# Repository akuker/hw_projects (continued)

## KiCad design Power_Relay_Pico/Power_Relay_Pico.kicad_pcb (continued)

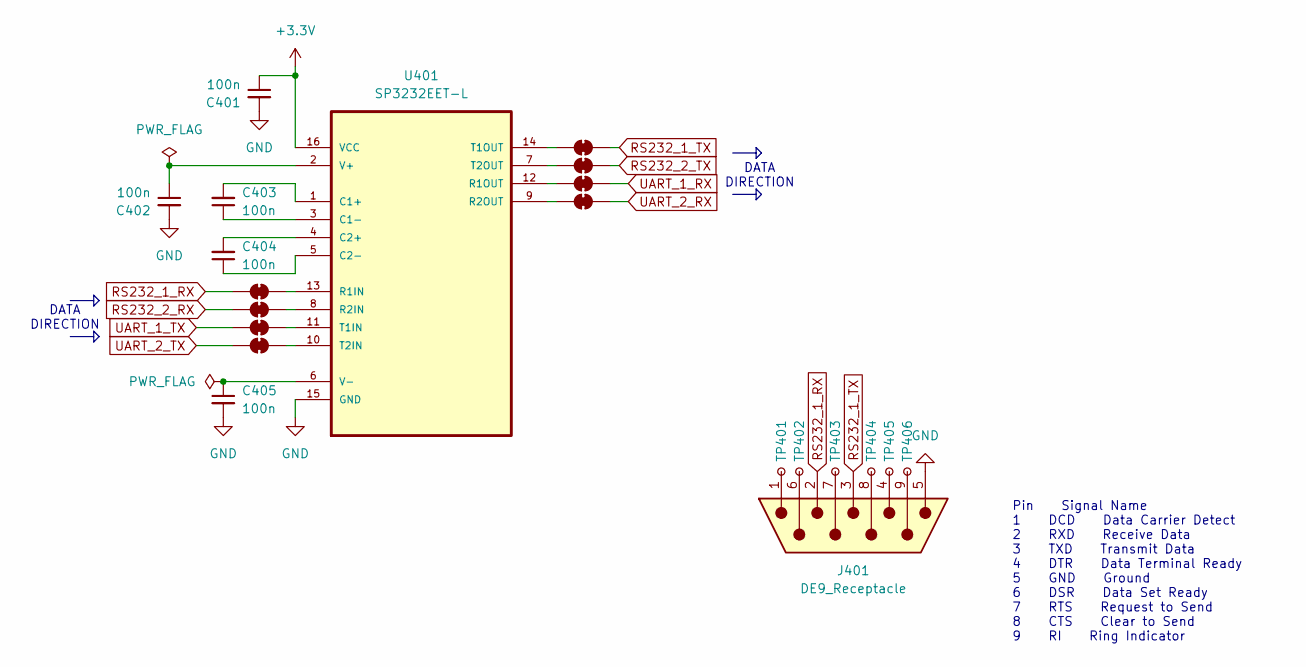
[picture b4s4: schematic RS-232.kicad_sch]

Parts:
C401, C402, C403, C404, C405: 100n; C_0603_1608Metric; LCSC C14663
J401: DE9_Receptacle; DSUB-9_Male_EdgeMount_P2.77mm; LCSC --
JP401, JP402, JP403, JP404, JP405, JP406, JP407, JP408: SolderJumper_2_Bridged; SolderJumper-2_P1.3mm_Bridged_RoundedPad1.0x1.5mm; LCSC --
TP401, TP402, TP403, TP404, TP405, TP406: TestPoint_Small; TestPoint_Pad_D1.0mm
U401: SP3232EET-L; TSSOP-16_4.4x5mm_P0.65mm; MPN SP3232EET-L; LCSC C13482

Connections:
+3.3V: C401.1, U401.16 (VCC); also elsewhere on the board
GND: C401.2, C402.2, C405.2, J401.5, U401.15 (GND); also elsewhere on the board
unnamed: J401.1, TP401.1
unnamed: J401.4, TP405.1
unnamed: J401.6, TP402.1
unnamed: J401.7, TP403.1
unnamed: J401.8, TP404.1
unnamed: J401.9, TP406.1
unnamed: JP401.1 (A), U401.14 (T1OUT)
unnamed: JP402.1 (A), U401.7 (T2OUT)
unnamed: JP403.1 (A), U401.12 (R1OUT)
unnamed: JP404.1 (A), U401.9 (R2OUT)
unnamed: JP405.2 (B), U401.13 (R1IN)
unnamed: JP406.2 (B), U401.8 (R2IN)
unnamed: JP407.2 (B), U401.11 (T1IN)
unnamed: JP408.2 (B), U401.10 (T2IN)
unnamed: C403.2, U401.1 (C1+)
unnamed: C403.1, U401.3 (C1-)
unnamed: C404.2, U401.4 (C2+)
unnamed: C404.1, U401.5 (C2-)
unnamed: C402.1, U401.2 (V+)
unnamed: C405.1, U401.6 (V-)
RS232_1_RX: J401.2, JP405.1 (A); also elsewhere on the board
RS232_1_TX: J401.3, JP401.2 (B); also elsewhere on the board
RS232_2_RX: JP406.1 (A); also elsewhere on the board
RS232_2_TX: JP402.2 (B); also elsewhere on the board
UART_1_RX: JP403.2 (B); also elsewhere on the board
UART_1_TX: JP407.1 (A); also elsewhere on the board
UART_2_RX: JP404.2 (B); also elsewhere on the board
UART_2_TX: JP408.1 (A); also elsewhere on the board

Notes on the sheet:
DATA DIRECTION
Pin Signal Name 1 DCD Data Carrier Detect 2 RXD Receive Data 3 TXD Transmit Data 4 DTR Data Terminal Ready 5 GND Ground 6 DSR Data Set Ready 7 RTS Request to Send 8 CTS Clear to Send 9 RI Ring Indicator

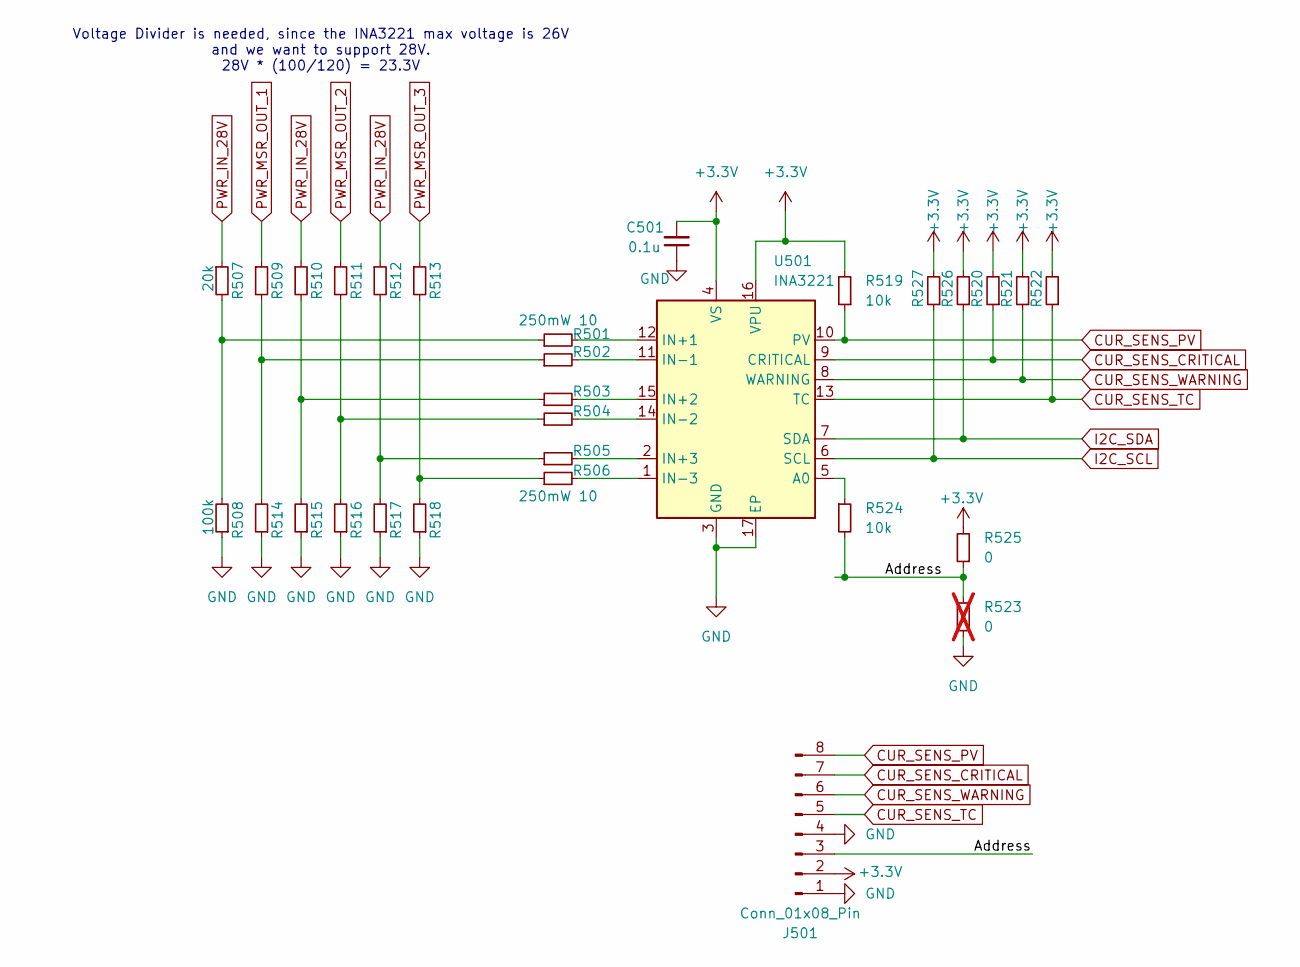
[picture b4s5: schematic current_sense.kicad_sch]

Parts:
C501: 0.1u; C_0603_1608Metric; LCSC C14663
J501: Conn_01x08_Pin; PinHeader_1x08_P2.54mm_Vertical; LCSC --
R501, R502, R503, R504, R505, R506: 250mW 10; R_1206_3216Metric; LCSC C17903
R507, R509, R510, R511, R512, R513: 20k; R_0603_1608Metric; LCSC C4184
R508, R514, R515, R516, R517, R518: 100k; R_0603_1608Metric; LCSC C25803
R519, R520, R521, R522, R524, R526, R527: 10k; R_0603_1608Metric; LCSC C25804
R523: 0; R_0603_1608Metric; LCSC C21189; not fitted
R525: 0; R_0603_1608Metric; LCSC C21189
U501: INA3221; Texas_RGV0016A_VQFN-16-1EP_4x4mm_P0.65mm_EP2.1x2.1mm; LCSC C181255

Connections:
+3.3V: C501.2, J501.2, R519.2, R520.2, R521.2, R522.2, R525.2, R526.2, R527.2, U501.4 (VS), U501.16 (VPU); also elsewhere on the board
/Current Sense/Address: J501.3, R523.2, R524.2, R525.1
CUR_SENS_CRITICAL: J501.7, R520.1, U501.9 (CRITICAL); also elsewhere on the board
CUR_SENS_PV: J501.8, R519.1, U501.10 (PV); also elsewhere on the board
CUR_SENS_TC: J501.5, R522.1, U501.13 (TC); also elsewhere on the board
CUR_SENS_WARNING: J501.6, R521.1, U501.8 (WARNING); also elsewhere on the board
GND: C501.1, J501.1, J501.4, R508.1, R514.1, R515.1, R516.1, R517.1, R518.1, R523.1, U501.3 (GND), U501.17 (EP); also elsewhere on the board
I2C_SCL: R527.1, U501.6 (SCL); also elsewhere on the board
I2C_SDA: R526.1, U501.7 (SDA); also elsewhere on the board
unnamed: R501.1, R507.2, R508.2
unnamed: R502.1, R509.2, R514.2
unnamed: R503.1, R510.2, R515.2
unnamed: R504.1, R511.2, R516.2
unnamed: R505.1, R512.2, R517.2
unnamed: R506.1, R513.2, R518.2
unnamed: R524.1, U501.5 (A0)
unnamed: R501.2, U501.12 (IN+1)
unnamed: R503.2, U501.15 (IN+2)
unnamed: R505.2, U501.2 (IN+3)
unnamed: R502.2, U501.11 (IN-1)
unnamed: R504.2, U501.14 (IN-2)
unnamed: R506.2, U501.1 (IN-3)
PWR_IN_28V: R507.1, R510.1, R512.1; also elsewhere on the board
PWR_MSR_OUT_1: R509.1; also elsewhere on the board
PWR_MSR_OUT_2: R511.1; also elsewhere on the board
PWR_MSR_OUT_3: R513.1; also elsewhere on the board

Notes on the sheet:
Voltage Divider is needed, since the INA3221 max voltage is 26V and we want to support 28V. 28V * (100/120) = 23.3V

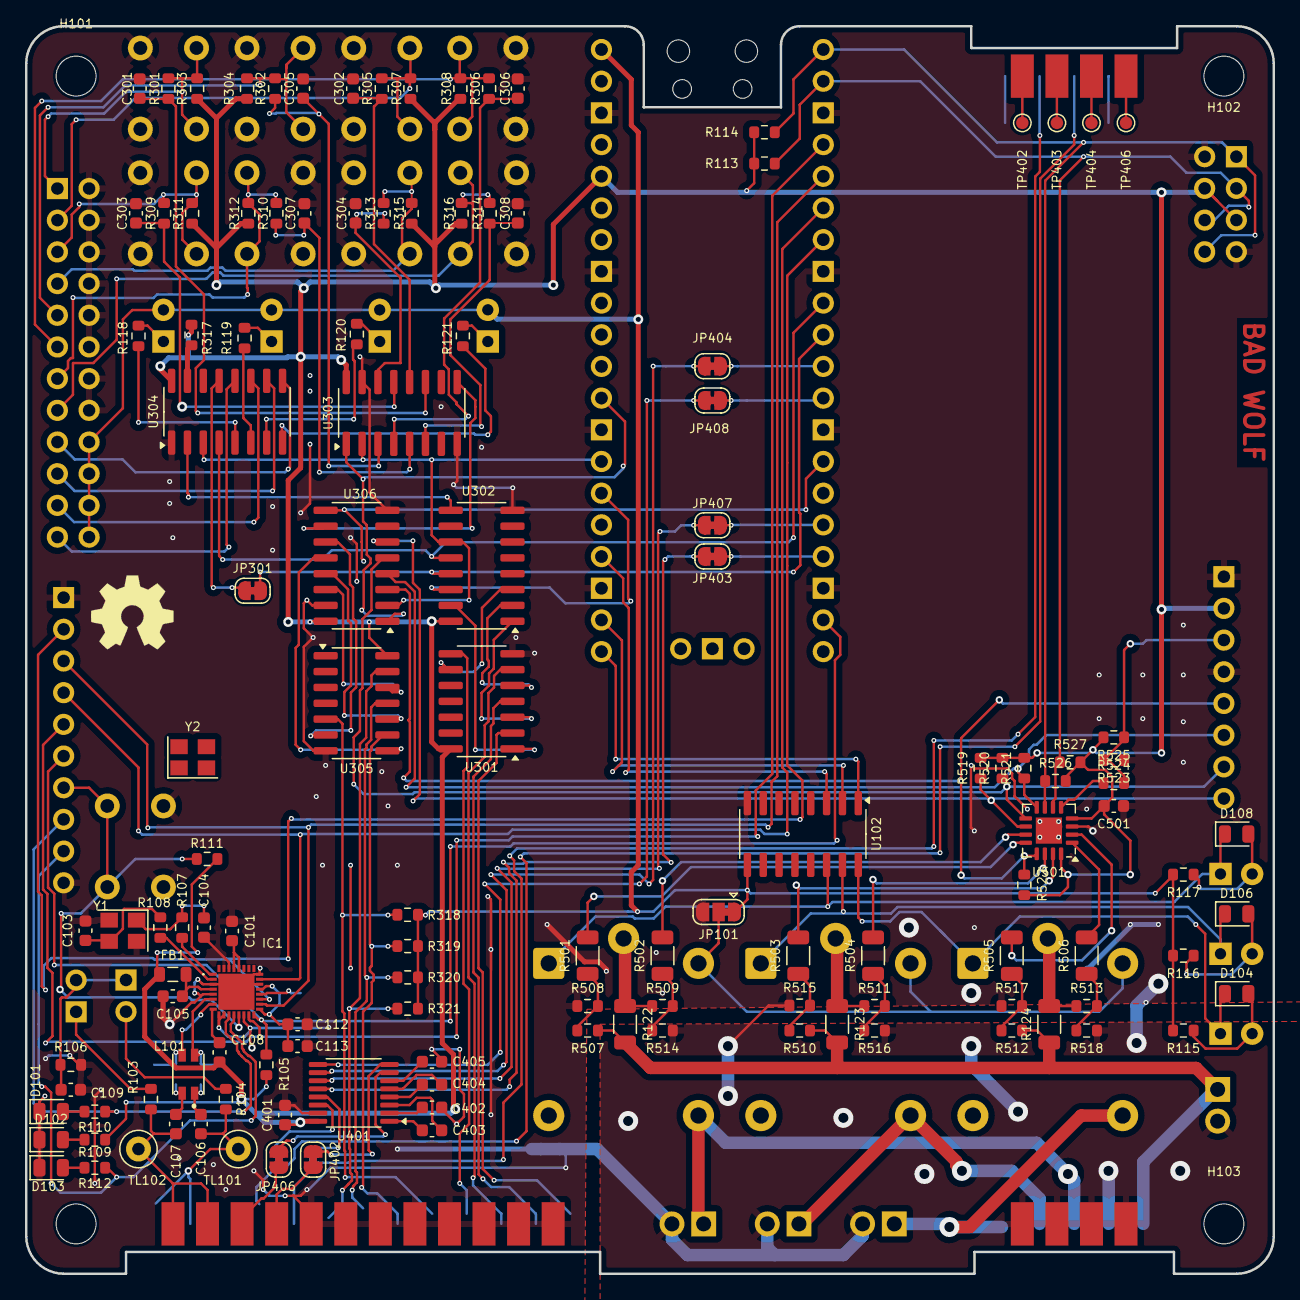
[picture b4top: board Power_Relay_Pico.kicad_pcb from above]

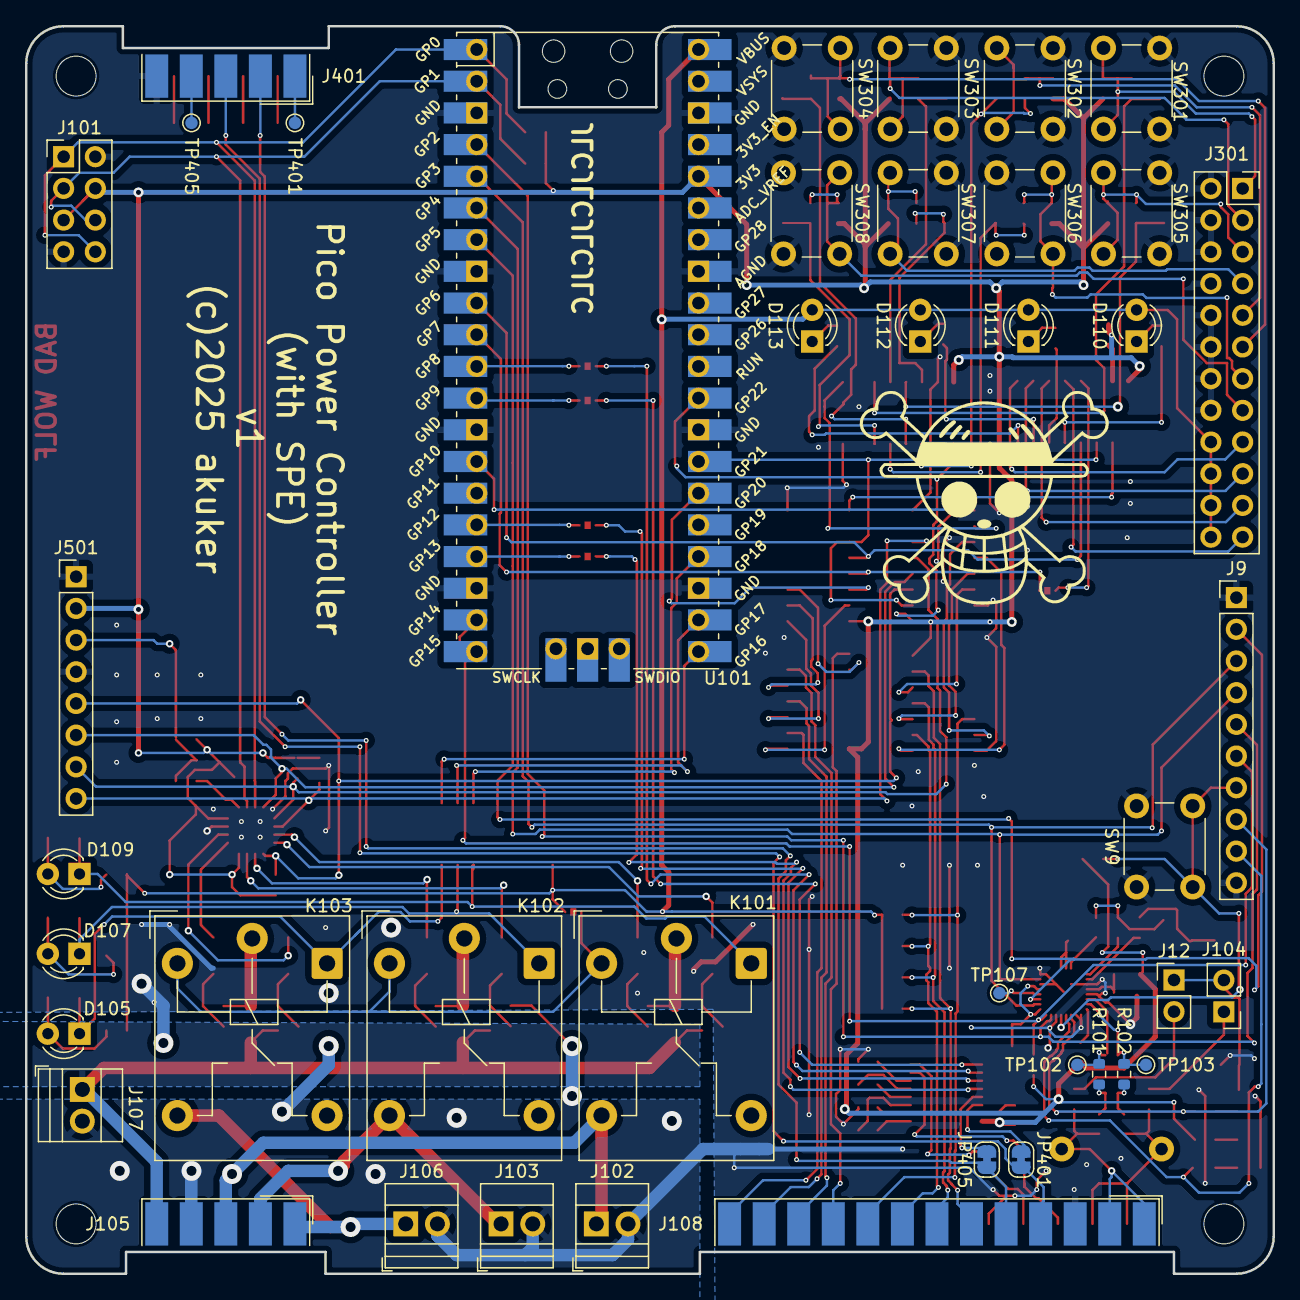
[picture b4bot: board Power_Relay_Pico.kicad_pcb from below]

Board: 2 copper layers, 100.0 x 100.0 mm, 174 parts (42 on the bottom side), 151 nets.

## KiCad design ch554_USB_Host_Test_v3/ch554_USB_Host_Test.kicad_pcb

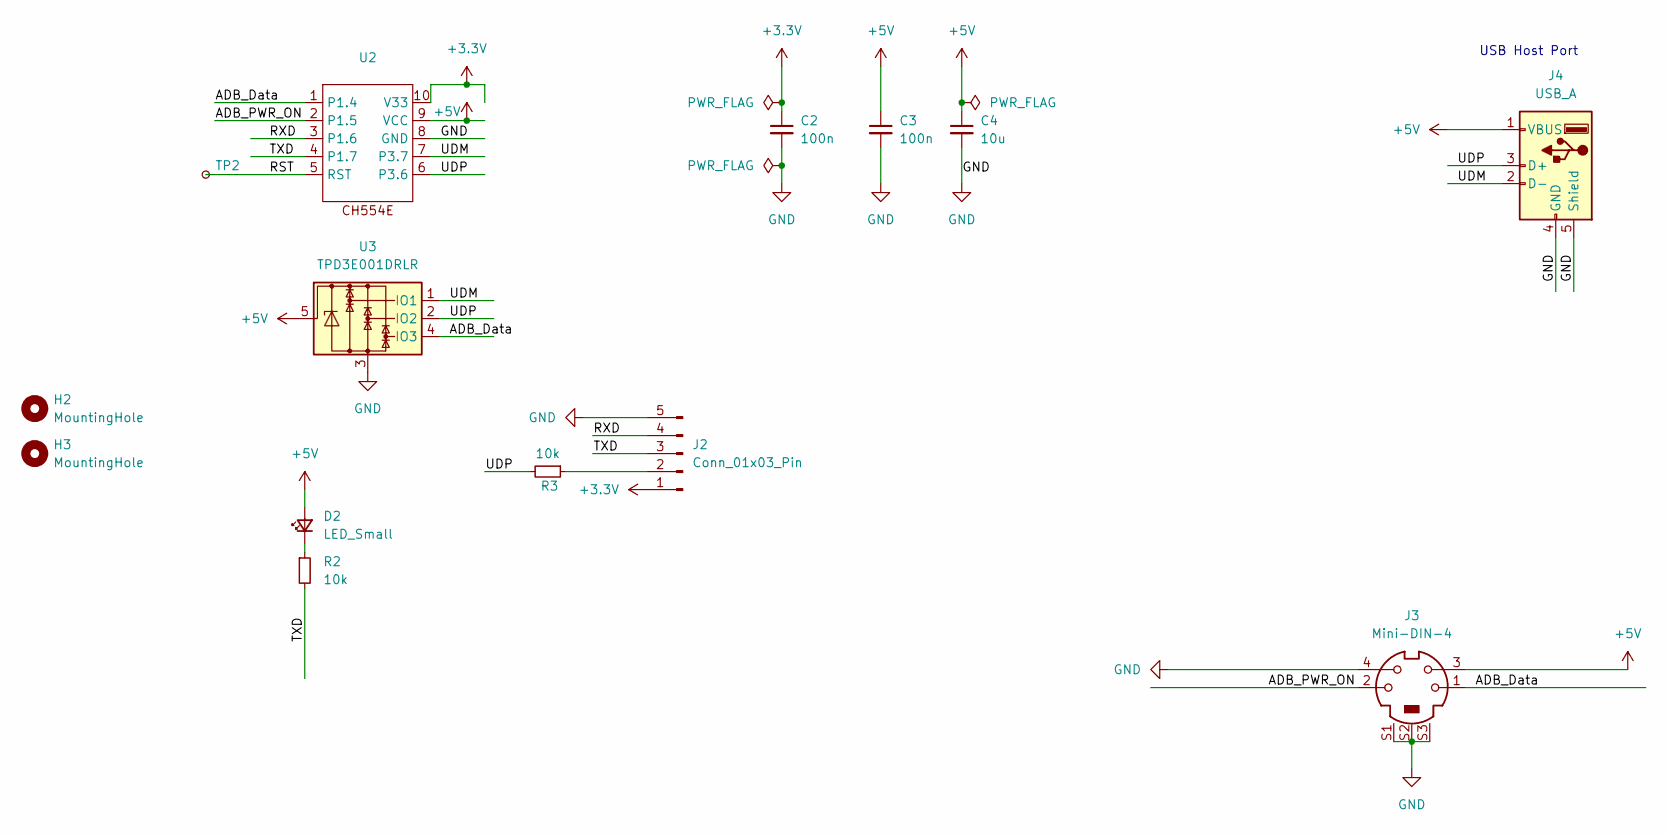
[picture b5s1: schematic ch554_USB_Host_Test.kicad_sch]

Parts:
C2, C3: 100n; C_0603_1608Metric_Pad1.08x0.95mm_HandSolder; LCSC C14663
C4: 10u; C_0603_1608Metric_Pad1.08x0.95mm_HandSolder; LCSC C96446
D2: LED_Small; LED_0603_1608Metric_Pad1.05x0.95mm_HandSolder; LCSC C2286
H2, H3: MountingHole; MountingHole_2.7mm_M2.5
J2: Conn_01x03_Pin; PinHeader_1x05_P2.54mm_Vertical
J3: Mini-DIN-4; CUI_MD2-40ST-SMT
J4: USB_A; USB_A_Molex_67643_Horizontal; LCSC C2346
R2, R3: 10k; R_0603_1608Metric_Pad0.98x0.95mm_HandSolder; LCSC C25804
TP2: TestPoint_Small; TestPoint_Pad_D1.0mm
U2: MSOP-10_3x3mm_P0.5mm; LCSC C111293
U3: TPD3E001DRLR; SOT-553; LCSC C2999113

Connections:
+3.3V: C2.1, J2.1, U2.10 (V33)
+5V: C3.1, C4.1, D2.2 (A), J3.3, J4.1 (VBUS), U2.9 (VCC), U3.5
/ADB_Data: J3.1, U2.1 (P1.4), U3.4 (IO3)
/ADB_PWR_ON: J3.2, U2.2 (P1.5)
/RST: TP2.1, U2.5 (RST)
/RXD: J2.4, U2.3 (P1.6)
/TXD: J2.3, R2.2, U2.4 (P1.7)
/UDM: J4.2 (D-), U2.7 (P3.7), U3.1 (IO1)
/UDP: J4.3 (D+), R3.2, U2.6 (P3.6), U3.2 (IO2)
GND: C2.2, C3.2, C4.2, J2.5, J3.4, J3.S1, J3.S2, J3.S3, J4.4 (GND), J4.5 (Shield), U2.8 (GND), U3.3
unnamed: D2.1 (K), R2.1
unnamed: J2.2, R3.1

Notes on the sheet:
USB Host Port

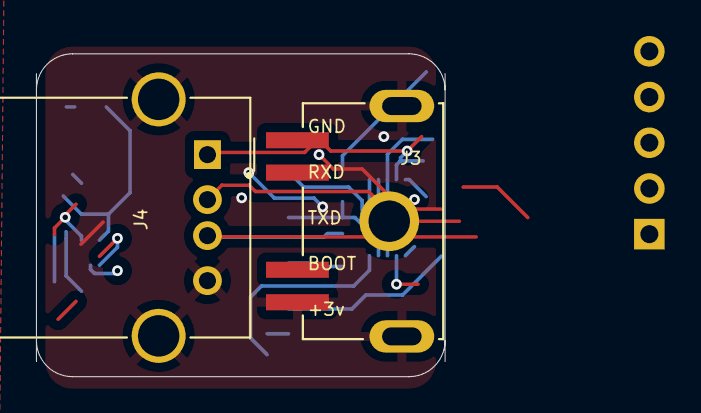
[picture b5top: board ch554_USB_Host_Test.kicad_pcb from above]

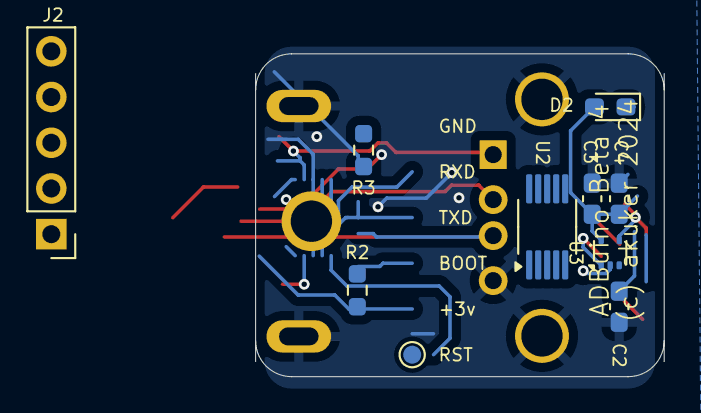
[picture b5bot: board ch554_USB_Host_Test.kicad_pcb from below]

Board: 2 copper layers, 22.7 x 17.9 mm, 13 parts (10 on the bottom side), 12 nets.

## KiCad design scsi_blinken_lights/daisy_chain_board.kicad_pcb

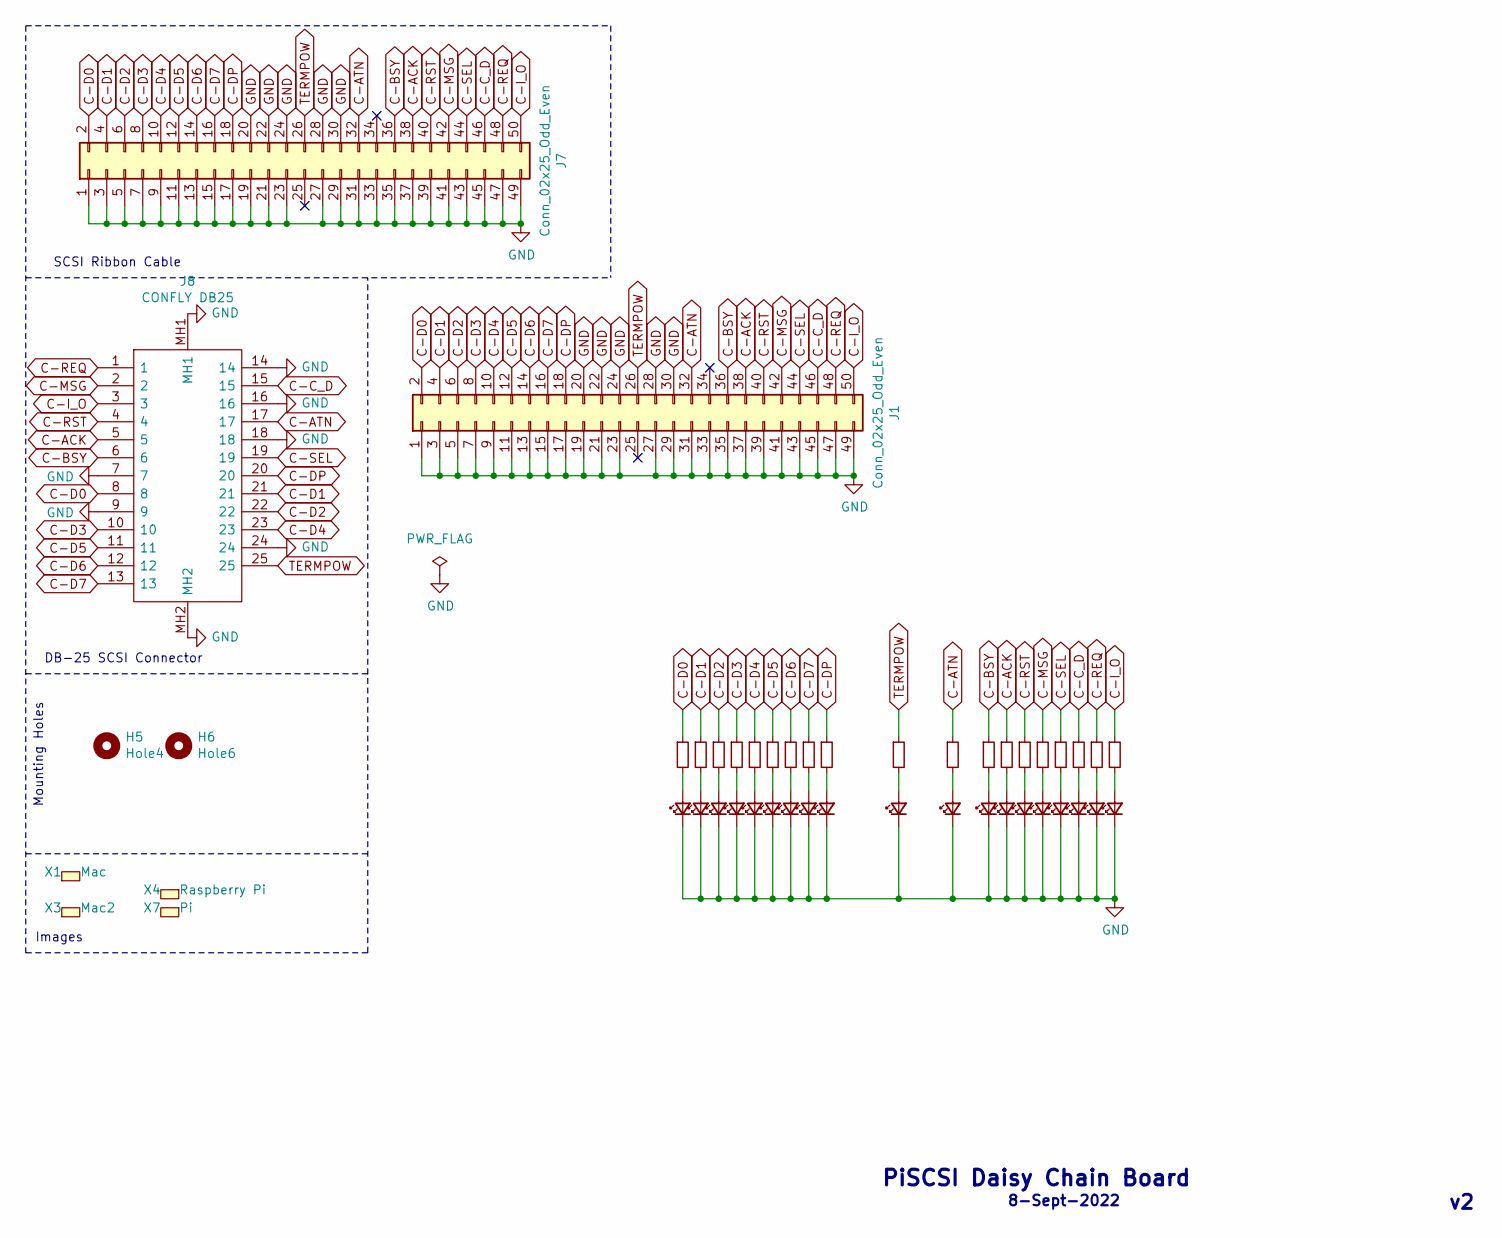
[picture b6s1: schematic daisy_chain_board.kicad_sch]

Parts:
D1, D2, D3, D4, D5, D6, D7, D8, D9, D12, D13, D14, D15, D16, D17, D18, D19, D20, D21: LED_Small; LED_0805_2012Metric; LCSC C2297
H5: Hole4; MountingHole_2.7mm
H6: Hole6; MountingHole_2.7mm
J1, J7: Conn_02x25_Odd_Even; PinHeader_2x25_P2.54mm_Vertical; LCSC C40024
J8: CONFLY DB25; L717SDB25PA4CH4F; Mouser Part Number 523-L717SDB25PA4CH4F
R1, R2, R3, R4, R5, R6, R7, R8, R9, R12, R13, R14, R15, R16, R17, R18, R19, R20, R21: R_Small; R_0805_2012Metric_Pad1.20x1.40mm_HandSolder; LCSC C17414
X1: Mac; mac_happy_small
X3: Mac2; mac_happy_small
X4: Raspberry Pi; pi_logo
X7: Pi; pi_logo

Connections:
C-ACK: J1.38, J7.38, J8.5, R15.1
C-ATN: J1.32, J7.32, J8.17, R13.1
C-BSY: J1.36, J7.36, J8.6, R14.1
C-C_D: J1.46, J7.46, J8.15, R19.1
C-D0: J1.2, J7.2, J8.8, R1.1
C-D1: J1.4, J7.4, J8.21, R2.1
C-D2: J1.6, J7.6, J8.22, R3.1
C-D3: J1.8, J7.8, J8.10, R4.1
C-D4: J1.10, J7.10, J8.23, R5.1
C-D5: J1.12, J7.12, J8.11, R6.1
C-D6: J1.14, J7.14, J8.12, R7.1
C-D7: J1.16, J7.16, J8.13, R8.1
C-DP: J1.18, J7.18, J8.20, R9.1
C-I_O: J1.50, J7.50, J8.3, R21.1
C-MSG: J1.42, J7.42, J8.2, R17.1
C-REQ: J1.48, J7.48, J8.1, R20.1
C-RST: J1.40, J7.40, J8.4, R16.1
C-SEL: J1.44, J7.44, J8.19, R18.1
GND: D1.1 (K), D2.1 (K), D3.1 (K), D4.1 (K), D5.1 (K), D6.1 (K), D7.1 (K), D8.1 (K), D9.1 (K), D12.1 (K), D13.1 (K), D14.1 (K), D15.1 (K), D16.1 (K), D17.1 (K), D18.1 (K), D19.1 (K), D20.1 (K), D21.1 (K), J1.1, J1.3, J1.5, J1.7, J1.9, J1.11, J1.13, J1.15, J1.17, J1.19, J1.20, J1.21, J1.22, J1.23, J1.24, J1.27, J1.28, J1.29, J1.30, J1.31, J1.33, J1.35, J1.37, J1.39, J1.41, J1.43, J1.45, J1.47, J1.49, J7.1, J7.3, J7.5, J7.7, J7.9, J7.11, J7.13, J7.15, J7.17, J7.19, J7.20, J7.21, J7.22, J7.23, J7.24, J7.27, J7.28, J7.29, J7.30, J7.31, J7.33, J7.35, J7.37, J7.39, J7.41, J7.43, J7.45, J7.47, J7.49, J8.7, J8.9, J8.14, J8.16, J8.18, J8.24, J8.MH1, J8.MH2
unnamed: D1.2 (A), R1.2
unnamed: D2.2 (A), R2.2
unnamed: D3.2 (A), R3.2
unnamed: D4.2 (A), R4.2
unnamed: D5.2 (A), R5.2
unnamed: D6.2 (A), R6.2
unnamed: D7.2 (A), R7.2
unnamed: D8.2 (A), R8.2
unnamed: D9.2 (A), R9.2
unnamed: D12.2 (A), R12.2
unnamed: D13.2 (A), R13.2
unnamed: D14.2 (A), R14.2
unnamed: D15.2 (A), R15.2
unnamed: D16.2 (A), R16.2
unnamed: D17.2 (A), R17.2
unnamed: D18.2 (A), R18.2
unnamed: D19.2 (A), R19.2
unnamed: D20.2 (A), R20.2
unnamed: D21.2 (A), R21.2
TERMPOW: J1.26, J7.26, J8.25, R12.1

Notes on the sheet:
DB-25 SCSI Connector
Images
8-Sept-2022
PiSCSI Daisy Chain Board
Mounting Holes
SCSI Ribbon Cable

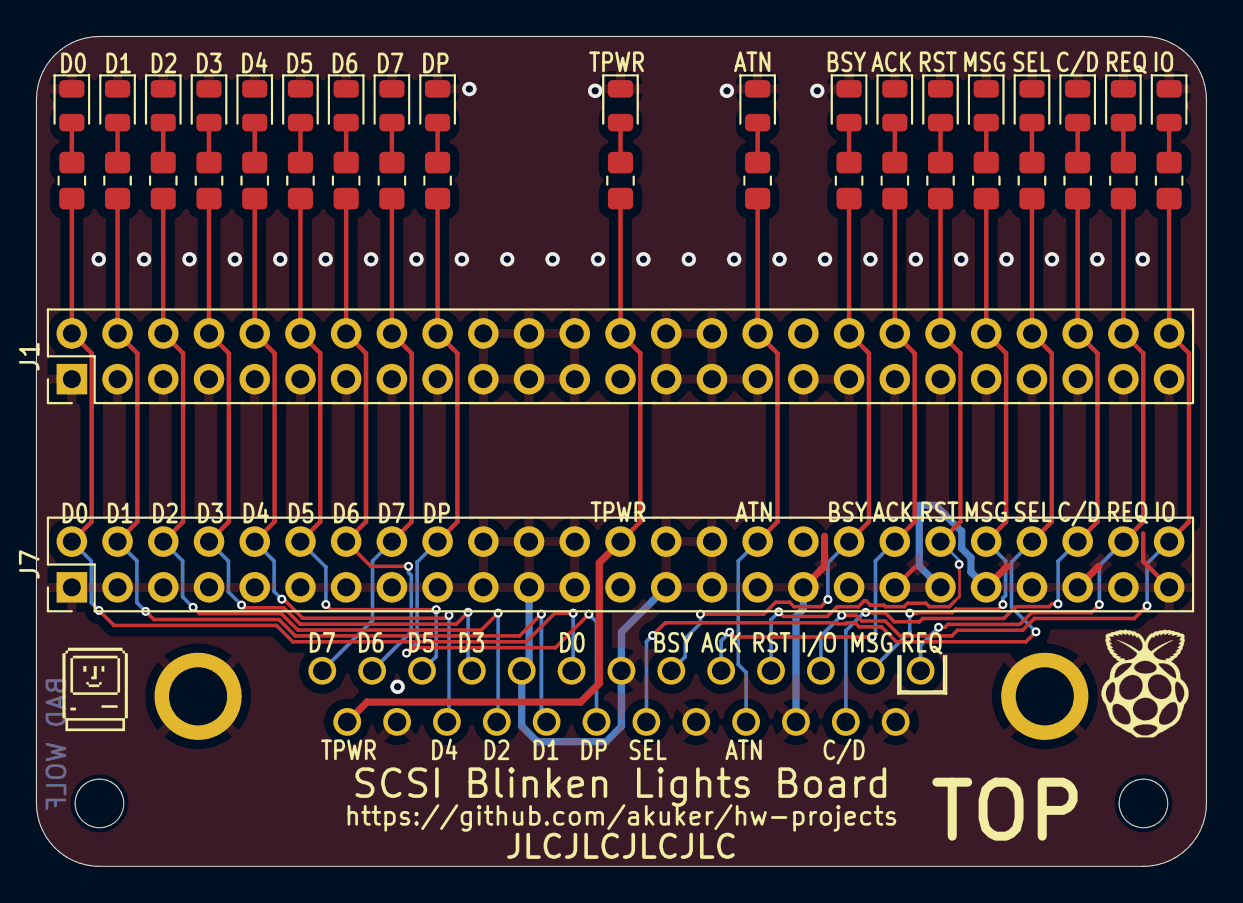
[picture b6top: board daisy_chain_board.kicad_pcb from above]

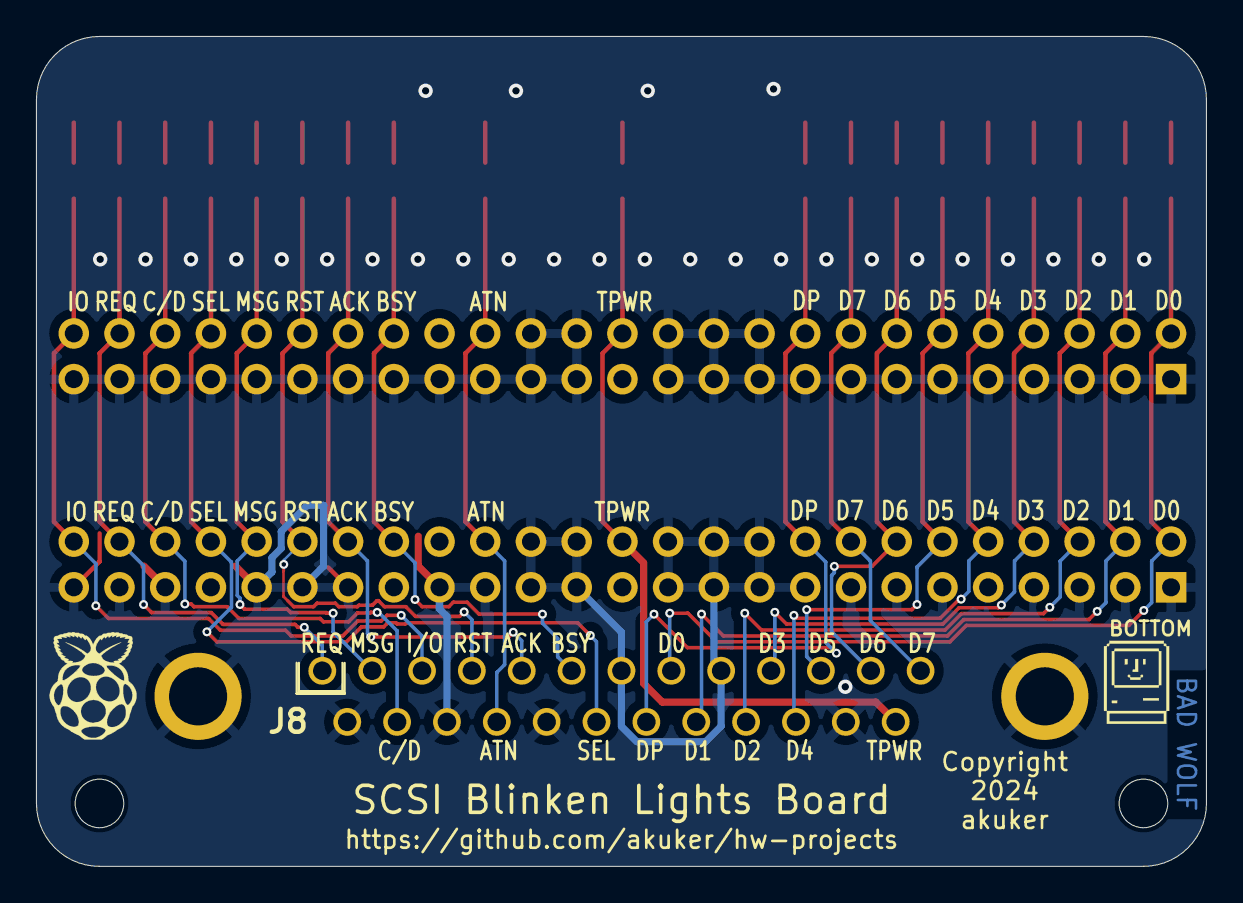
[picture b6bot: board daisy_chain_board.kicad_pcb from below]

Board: 2 copper layers, 65.0 x 46.1 mm, 47 parts (3 on the bottom side), 39 nets.

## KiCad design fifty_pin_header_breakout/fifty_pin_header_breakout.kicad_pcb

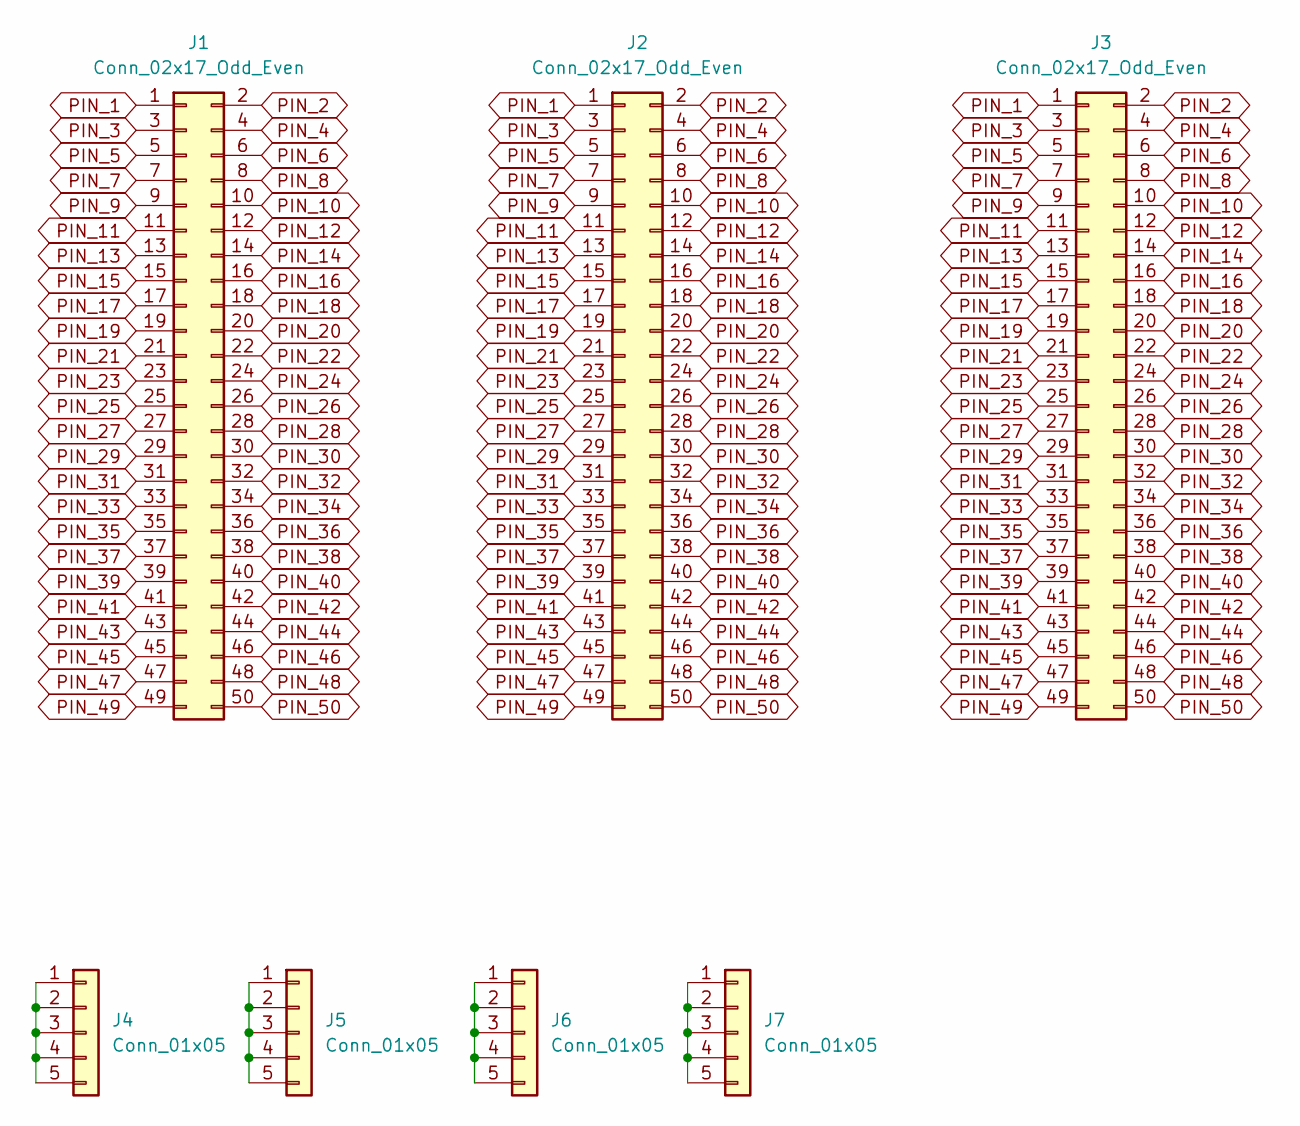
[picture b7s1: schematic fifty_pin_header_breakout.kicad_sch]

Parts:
J1, J2, J3: Conn_02x17_Odd_Even; PinHeader_2x25_P2.54mm_Vertical
J4, J5, J6, J7: Conn_01x05; PinHeader_1x05_P2.54mm_Vertical

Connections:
unnamed: J4.1, J4.2, J4.3, J4.4, J4.5
unnamed: J5.1, J5.2, J5.3, J5.4, J5.5
unnamed: J6.1, J6.2, J6.3, J6.4, J6.5
unnamed: J7.1, J7.2, J7.3, J7.4, J7.5
PIN_1: J1.1, J2.1, J3.1
PIN_2: J1.2, J2.2, J3.2
PIN_3: J1.3, J2.3, J3.3
PIN_4: J1.4, J2.4, J3.4
PIN_5: J1.5, J2.5, J3.5
PIN_6: J1.6, J2.6, J3.6
PIN_7: J1.7, J2.7, J3.7
PIN_8: J1.8, J2.8, J3.8
PIN_9: J1.9, J2.9, J3.9
PIN_10: J1.10, J2.10, J3.10
PIN_11: J1.11, J2.11, J3.11
PIN_12: J1.12, J2.12, J3.12
PIN_13: J1.13, J2.13, J3.13
PIN_14: J1.14, J2.14, J3.14
PIN_15: J1.15, J2.15, J3.15
PIN_16: J1.16, J2.16, J3.16
PIN_17: J1.17, J2.17, J3.17
PIN_18: J1.18, J2.18, J3.18
PIN_19: J1.19, J2.19, J3.19
PIN_20: J1.20, J2.20, J3.20
PIN_21: J1.21, J2.21, J3.21
PIN_22: J1.22, J2.22, J3.22
PIN_23: J1.23, J2.23, J3.23
PIN_24: J1.24, J2.24, J3.24
PIN_25: J1.25, J2.25, J3.25
PIN_26: J1.26, J2.26, J3.26
PIN_27: J1.27, J2.27, J3.27
PIN_28: J1.28, J2.28, J3.28
PIN_29: J1.29, J2.29, J3.29
PIN_30: J1.30, J2.30, J3.30
PIN_31: J1.31, J2.31, J3.31
PIN_32: J1.32, J2.32, J3.32
PIN_33: J1.33, J2.33, J3.33
PIN_34: J1.34, J2.34, J3.34
PIN_35: J1.35, J2.35, J3.35
PIN_36: J1.36, J2.36, J3.36
PIN_37: J1.37, J2.37, J3.37
PIN_38: J1.38, J2.38, J3.38
PIN_39: J1.39, J2.39, J3.39
PIN_40: J1.40, J2.40, J3.40
PIN_41: J1.41, J2.41, J3.41
PIN_42: J1.42, J2.42, J3.42
PIN_43: J1.43, J2.43, J3.43
PIN_44: J1.44, J2.44, J3.44
PIN_45: J1.45, J2.45, J3.45
PIN_46: J1.46, J2.46, J3.46
PIN_47: J1.47, J2.47, J3.47
PIN_48: J1.48, J2.48, J3.48
PIN_49: J1.49, J2.49, J3.49
PIN_50: J1.50, J2.50, J3.50

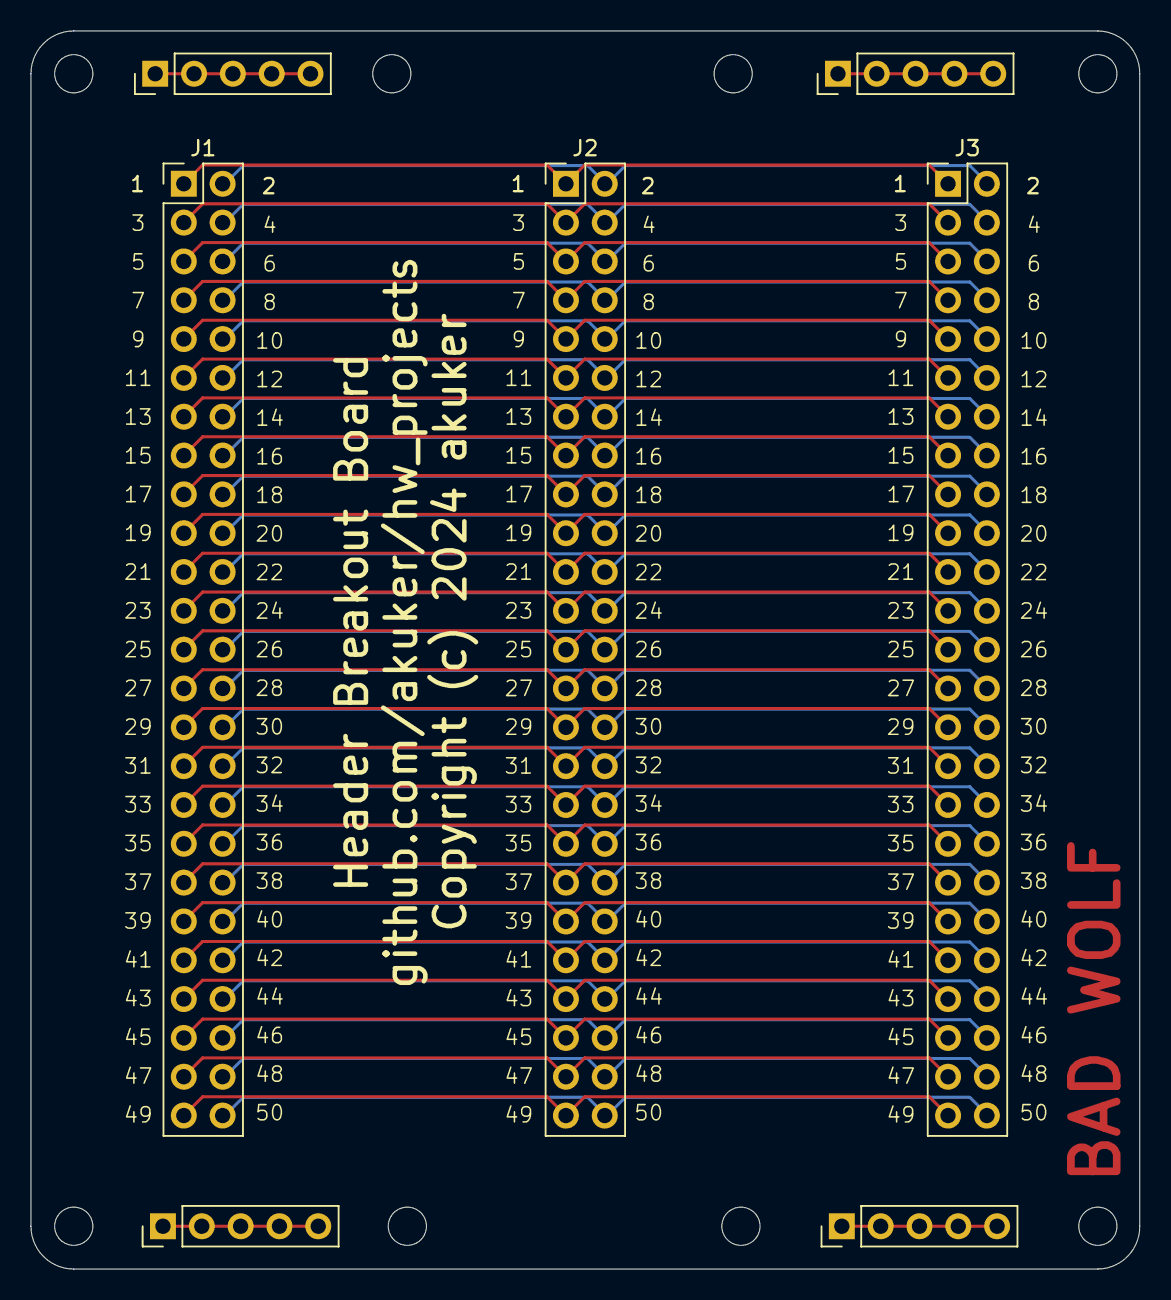
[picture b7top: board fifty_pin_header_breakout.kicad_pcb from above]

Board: 2 copper layers, 72.5 x 81.0 mm, 7 parts (0 on the bottom side), 54 nets.

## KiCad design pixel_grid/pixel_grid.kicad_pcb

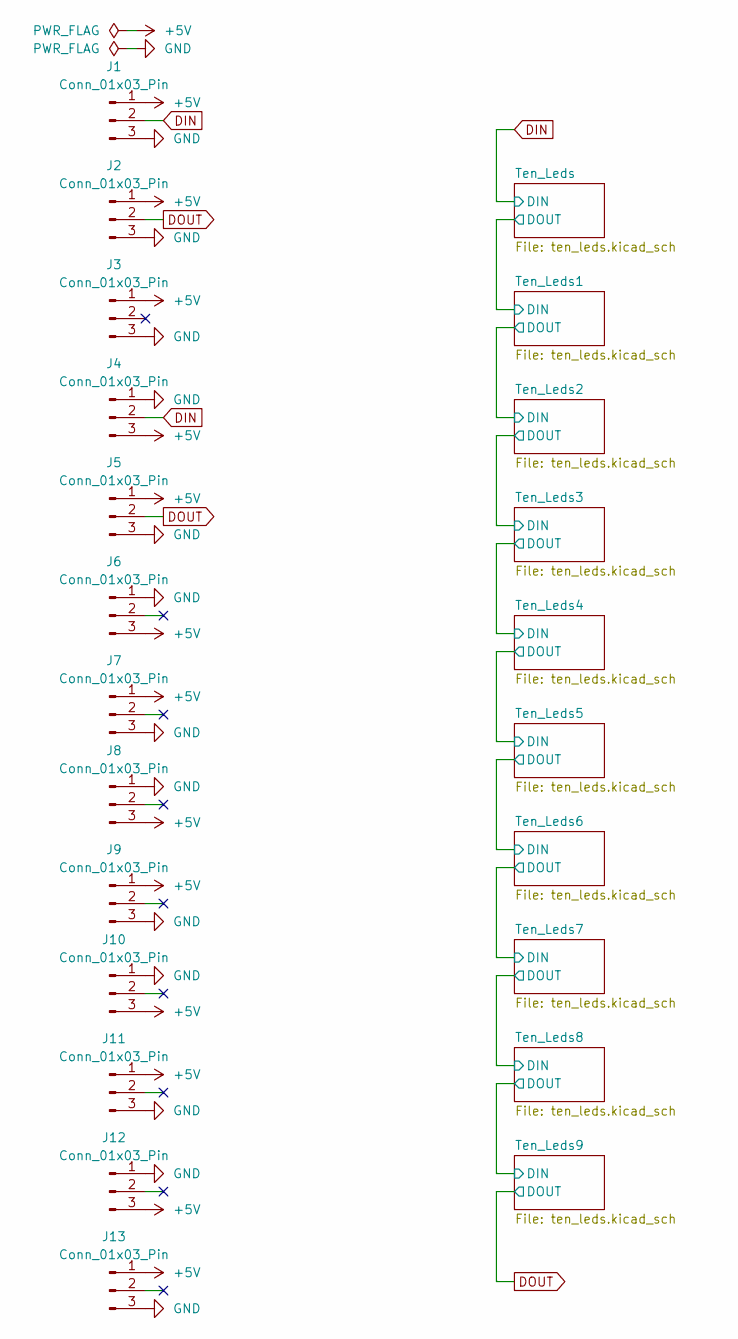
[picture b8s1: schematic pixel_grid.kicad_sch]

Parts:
J1, J2, J3: Conn_01x03_Pin; JST_PH_B3B-PH-K_1x03_P2.00mm_Vertical
J4, J5, J6, J7, J8, J9, J10, J11, J12, J13: Conn_01x03_Pin; Addr_Led_Side_Conn

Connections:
+5V: J1.1, J2.1, J3.1, J4.3, J5.1, J6.3, J7.1, J8.3, J9.1, J10.3, J11.1, J12.3, J13.1; also elsewhere on the board
DIN: J1.2, J4.2; also elsewhere on the board
DOUT: J2.2, J5.2; also elsewhere on the board
GND: J1.3, J2.3, J3.3, J4.1, J5.3, J6.1, J7.3, J8.1, J9.3, J10.1, J11.3, J12.1, J13.3; also elsewhere on the board
